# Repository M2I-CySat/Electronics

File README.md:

# Electronics - bits or volts yadda yadda

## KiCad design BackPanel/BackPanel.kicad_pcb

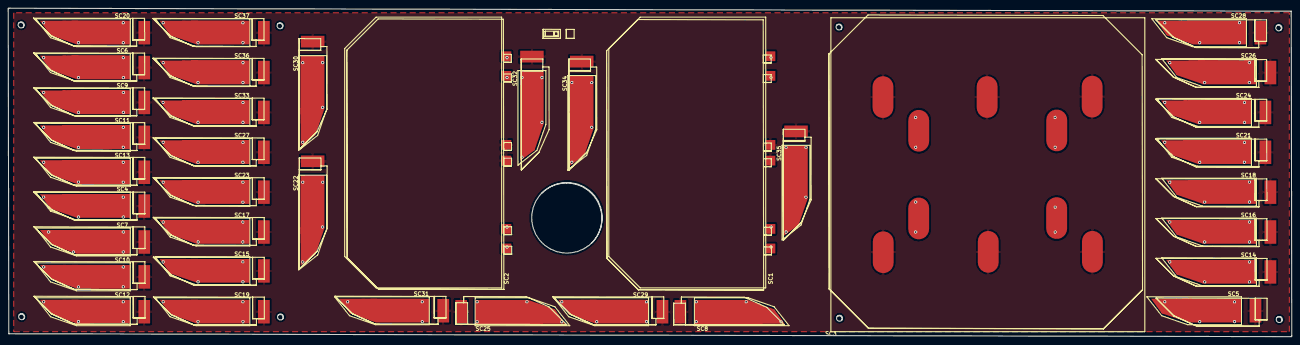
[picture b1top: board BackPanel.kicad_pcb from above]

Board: 2 copper layers, 327.1 x 83.7 mm, 37 parts (0 on the bottom side), 2 nets, no tracks yet.

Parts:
SC1, SC2: Solar_Cell; Spectrolab
SC3: Solar_Cell; ISS_SolarCell
SC4, SC5, SC6, SC7, SC8, SC9, SC10, SC11, SC12, SC13, SC14, SC15, SC16, SC17, SC18, SC19, SC20, SC21, SC22, SC23, SC24, SC25, SC26, SC27, SC28, SC29, SC30, SC31, SC32, SC33, SC34, SC35, SC36, SC37: Solar_Cell; TriSelectSolarPanel

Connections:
VCC: SC1.1, SC2.1, SC3.1, SC4.1, SC5.1, SC6.1, SC7.1, SC8.1, SC9.1, SC10.1, SC11.1, SC12.1, SC13.1, SC14.1, SC15.1, SC16.1, SC17.1, SC18.1, SC19.1, SC20.1, SC21.1, SC22.1, SC23.1, SC24.1, SC25.1, SC26.1, SC27.1, SC28.1, SC29.1, SC30.1, SC31.1, SC32.1, SC33.1, SC34.1, SC35.1, SC36.1, SC37.1
VSS: SC1.2, SC2.2, SC3.2, SC4.2, SC5.2, SC6.2, SC7.2, SC8.2, SC9.2, SC10.2, SC11.2, SC12.2, SC13.2, SC14.2, SC15.2, SC16.2, SC17.2, SC18.2, SC19.2, SC20.2, SC21.2, SC22.2, SC23.2, SC24.2, SC25.2, SC26.2, SC27.2, SC28.2, SC29.2, SC30.2, SC31.2, SC32.2, SC33.2, SC34.2, SC35.2, SC36.2, SC37.2

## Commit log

2018-08-28 First:
2018-08-28 Adding powerburn board
2018-09-08 Playing with submodules
2018-09-08 Added submodules
2018-09-09 Removed redundancy, redundancy
